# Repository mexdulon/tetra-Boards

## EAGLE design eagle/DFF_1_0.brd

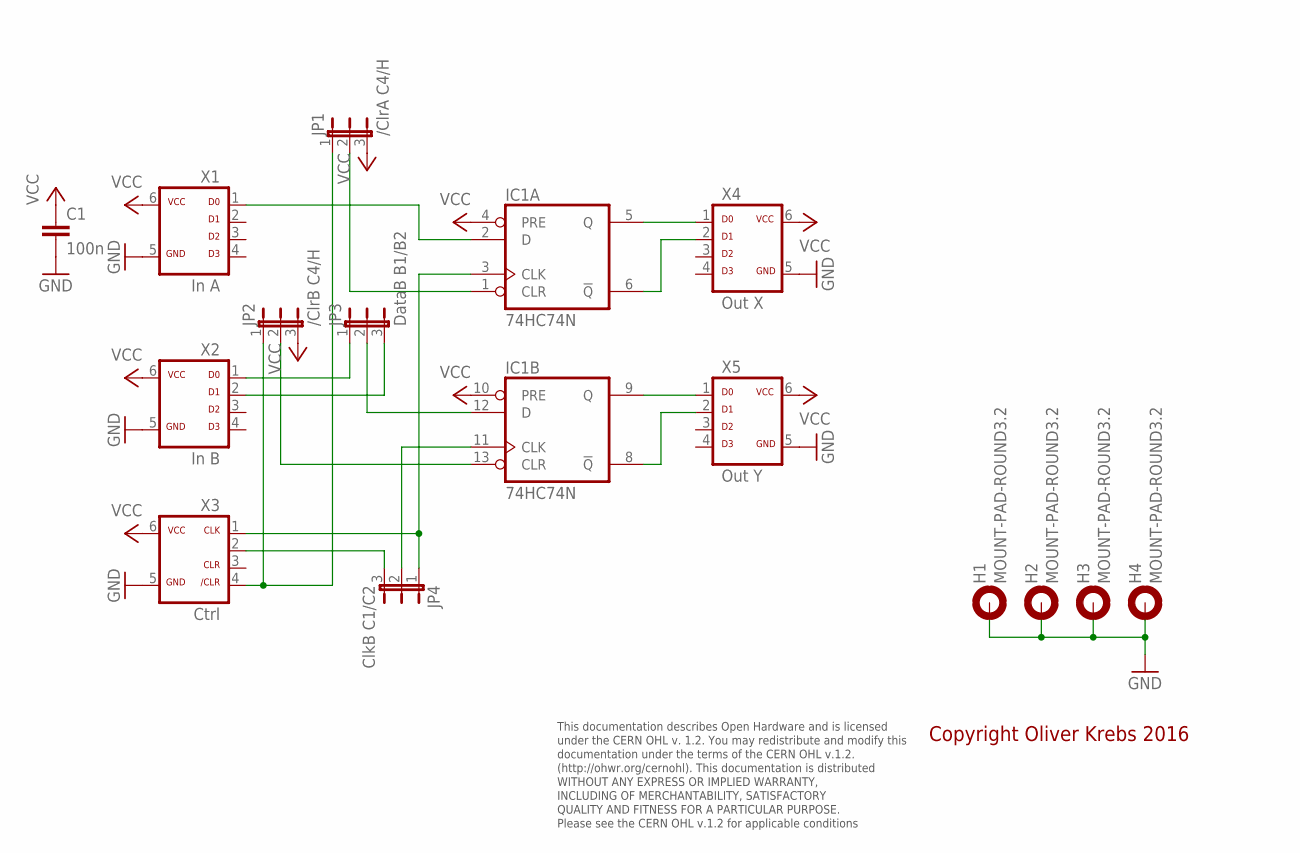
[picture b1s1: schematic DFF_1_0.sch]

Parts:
C1: 100n; C050-025X075
H1, H2, H3, H4: MOUNT-PAD-ROUND3.2; 3,2-PAD
IC1: 74HC74N; DIL14
JP1: /ClrA C4/H; JP2-U
JP2: /ClrB C4/H; JP2-U
JP3: DataB B1/B2; JP2-U
JP4: ClkB C1/C2; JP2-U
X1: In A; ML-6
X2: In B; ML-6
X3: Ctrl; ML-6
X4: Out X; ML-6
X5: Out Y; ML-6

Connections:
GND: C1.2, H1.B3,2, H2.B3,2, H3.B3,2, H4.B3,2, IC1.7 (GND), X1.5, X2.5, X3.5, X4.5, X5.5
unnamed: IC1.2 (D), X1.1
unnamed: IC1.3 (CLK), JP4.1, X3.1
unnamed: IC1.11 (CLK), JP4.2
unnamed: IC1.12 (D), JP3.2
unnamed: IC1.13 (CLR), JP2.2
unnamed: IC1.1 (CLR), JP1.2
unnamed: IC1.5 (Q), X4.1
unnamed: IC1.6 (!Q), X4.2
unnamed: IC1.9 (Q), X5.1
unnamed: IC1.8 (!Q), X5.2
unnamed: JP1.1, JP2.1, X3.4
unnamed: JP3.1, X2.1
unnamed: JP3.3, X2.2
unnamed: JP4.3, X3.2
VCC: C1.1, IC1.4 (PRE), IC1.10 (PRE), IC1.14 (VCC), JP1.3, JP2.3, X1.6, X2.6, X3.6, X4.6, X5.6

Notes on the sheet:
This documentation describes Open Hardware and is licensed under the CERN OHL v. 1.2. You may redistribute and modify this documentation under the terms of the CERN OHL v.1.2. (http://ohwr.org/cernohl). This documentation is distributed WITHOUT ANY EXPRESS OR IMPLIED WARRANTY, INCLUDING OF MERCHANT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
Copyright Oliver Krebs 2016

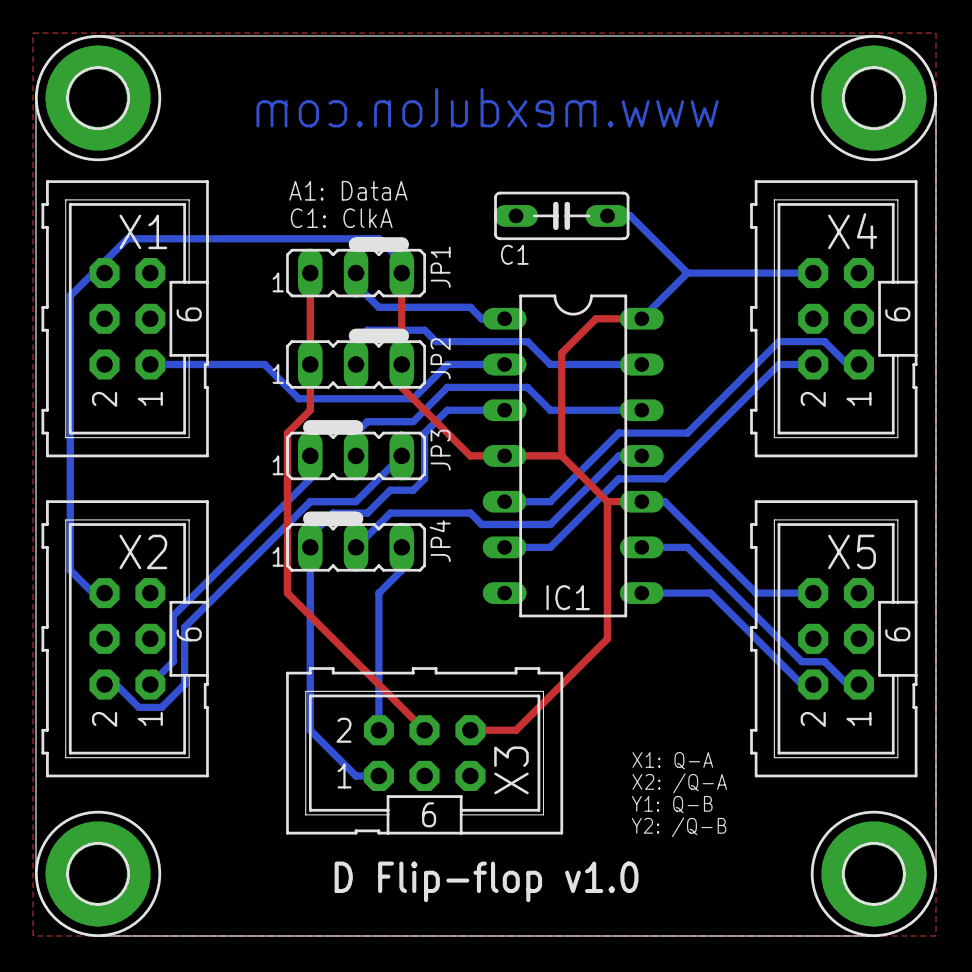
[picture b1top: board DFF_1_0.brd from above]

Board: 2 copper layers, 50.0 x 50.0 mm, 15 parts (0 on the bottom side), 16 nets.

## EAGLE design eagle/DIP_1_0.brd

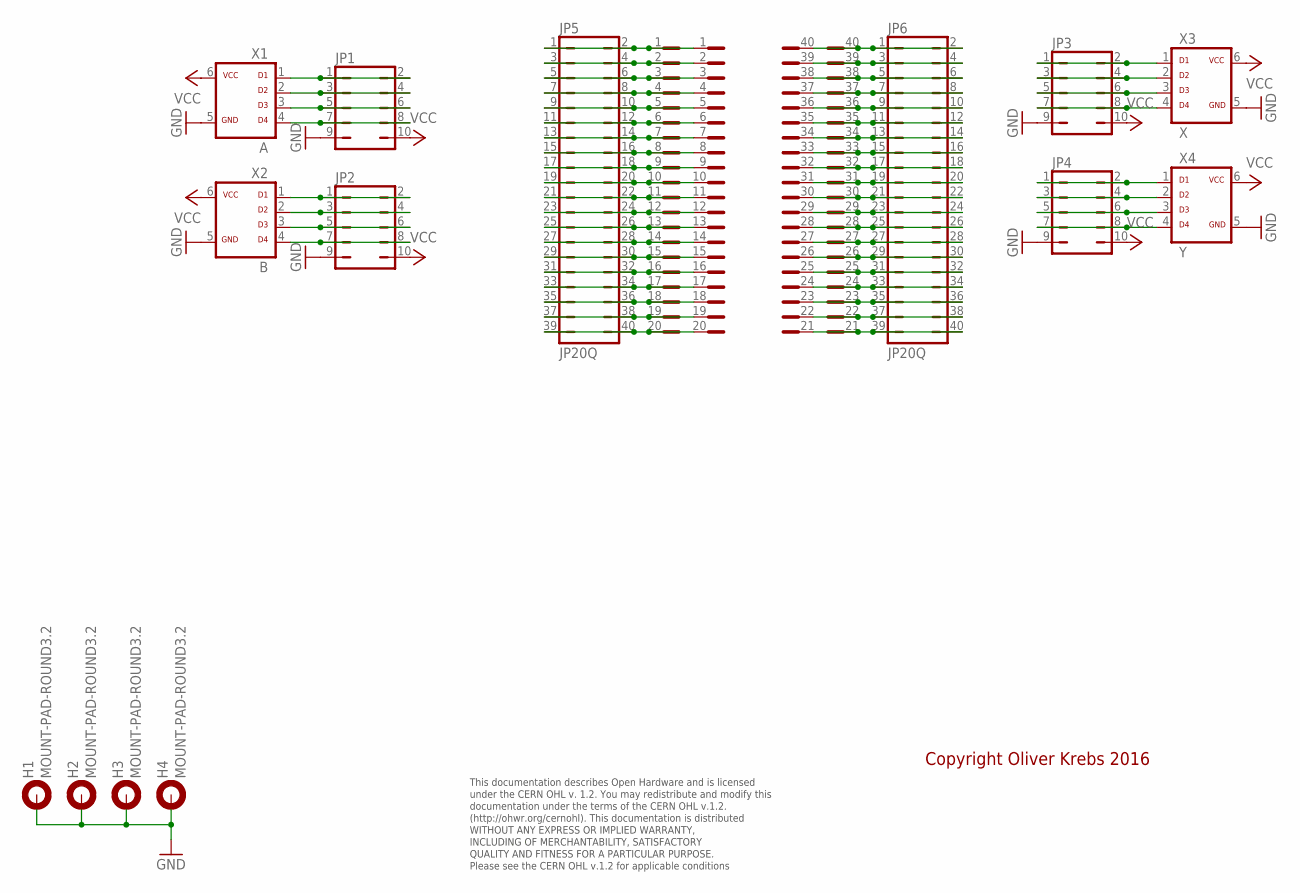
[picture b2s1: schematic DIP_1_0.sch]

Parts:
H1, H2, H3, H4: MOUNT-PAD-ROUND3.2; 3,2-PAD
JP1, JP2, JP3, JP4: JP5Q
JP5, JP6: JP20Q
X1: A; ML-6
X2: B; ML-6
X3: X; ML-6
X4: Y; ML-6
X5: DIL40-3
X6: DIL40-6

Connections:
GND: H1.B3,2, H2.B3,2, H3.B3,2, H4.B3,2, JP1.9, JP2.9, JP3.9, JP4.9, X1.5, X2.5, X3.5, X4.5
unnamed: JP3.1, JP3.2, X3.1
unnamed: JP3.3, JP3.4, X3.2
unnamed: JP3.5, JP3.6, X3.3
unnamed: JP3.7, JP3.8, X3.4
unnamed: JP4.1, JP4.2, X4.1
unnamed: JP4.3, JP4.4, X4.2
unnamed: JP4.5, JP4.6, X4.3
unnamed: JP4.7, JP4.8, X4.4
unnamed: JP1.1, JP1.2, X1.1
unnamed: JP1.3, JP1.4, X1.2
unnamed: JP1.5, JP1.6, X1.3
unnamed: JP1.7, JP1.8, X1.4
unnamed: JP2.1, JP2.2, X2.1
unnamed: JP2.3, JP2.4, X2.2
unnamed: JP2.5, JP2.6, X2.3
unnamed: JP2.7, JP2.8, X2.4
unnamed: JP5.1, JP5.2, X5.1, X6.1
unnamed: JP5.3, JP5.4, X5.2, X6.2
unnamed: JP5.5, JP5.6, X5.3, X6.3
unnamed: JP5.7, JP5.8, X5.4, X6.4
unnamed: JP5.9, JP5.10, X5.5, X6.5
unnamed: JP5.11, JP5.12, X5.6, X6.6
unnamed: JP5.13, JP5.14, X5.7, X6.7
unnamed: JP5.15, JP5.16, X5.8, X6.8
unnamed: JP5.17, JP5.18, X5.9, X6.9
unnamed: JP5.19, JP5.20, X5.10, X6.10
unnamed: JP5.21, JP5.22, X5.11, X6.11
unnamed: JP5.23, JP5.24, X5.12, X6.12
unnamed: JP5.25, JP5.26, X5.13, X6.13
unnamed: JP5.27, JP5.28, X5.14, X6.14
unnamed: JP5.29, JP5.30, X5.15, X6.15
unnamed: JP5.31, JP5.32, X5.16, X6.16
unnamed: JP5.33, JP5.34, X5.17, X6.17
unnamed: JP5.35, JP5.36, X5.18, X6.18
unnamed: JP5.37, JP5.38, X5.19, X6.19
unnamed: JP5.39, JP5.40, X5.20, X6.20
unnamed: JP6.1, JP6.2, X5.40, X6.40
unnamed: JP6.3, JP6.4, X5.39, X6.39
unnamed: JP6.5, JP6.6, X5.38, X6.38
unnamed: JP6.7, JP6.8, X5.37, X6.37
unnamed: JP6.9, JP6.10, X5.36, X6.36
unnamed: JP6.11, JP6.12, X5.35, X6.35
unnamed: JP6.13, JP6.14, X5.34, X6.34
unnamed: JP6.15, JP6.16, X5.33, X6.33
unnamed: JP6.17, JP6.18, X5.32, X6.32
unnamed: JP6.19, JP6.20, X5.31, X6.31
unnamed: JP6.21, JP6.22, X5.30, X6.30
unnamed: JP6.23, JP6.24, X5.29, X6.29
unnamed: JP6.25, JP6.26, X5.28, X6.28
unnamed: JP6.27, JP6.28, X5.27, X6.27
unnamed: JP6.29, JP6.30, X5.26, X6.26
unnamed: JP6.31, JP6.32, X5.25, X6.25
unnamed: JP6.33, JP6.34, X5.24, X6.24
unnamed: JP6.35, JP6.36, X5.23, X6.23
unnamed: JP6.37, JP6.38, X5.22, X6.22
unnamed: JP6.39, JP6.40, X5.21, X6.21
VCC: JP1.10, JP2.10, JP3.10, JP4.10, X1.6, X2.6, X3.6, X4.6

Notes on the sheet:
This documentation describes Open Hardware and is licensed under the CERN OHL v. 1.2. You may redistribute and modify this documentation under the terms of the CERN OHL v.1.2. (http://ohwr.org/cernohl). This documentation is distributed WITHOUT ANY EXPRESS OR IMPLIED WARRANTY, INCLUDING OF MERCHANT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
Copyright Oliver Krebs 2016

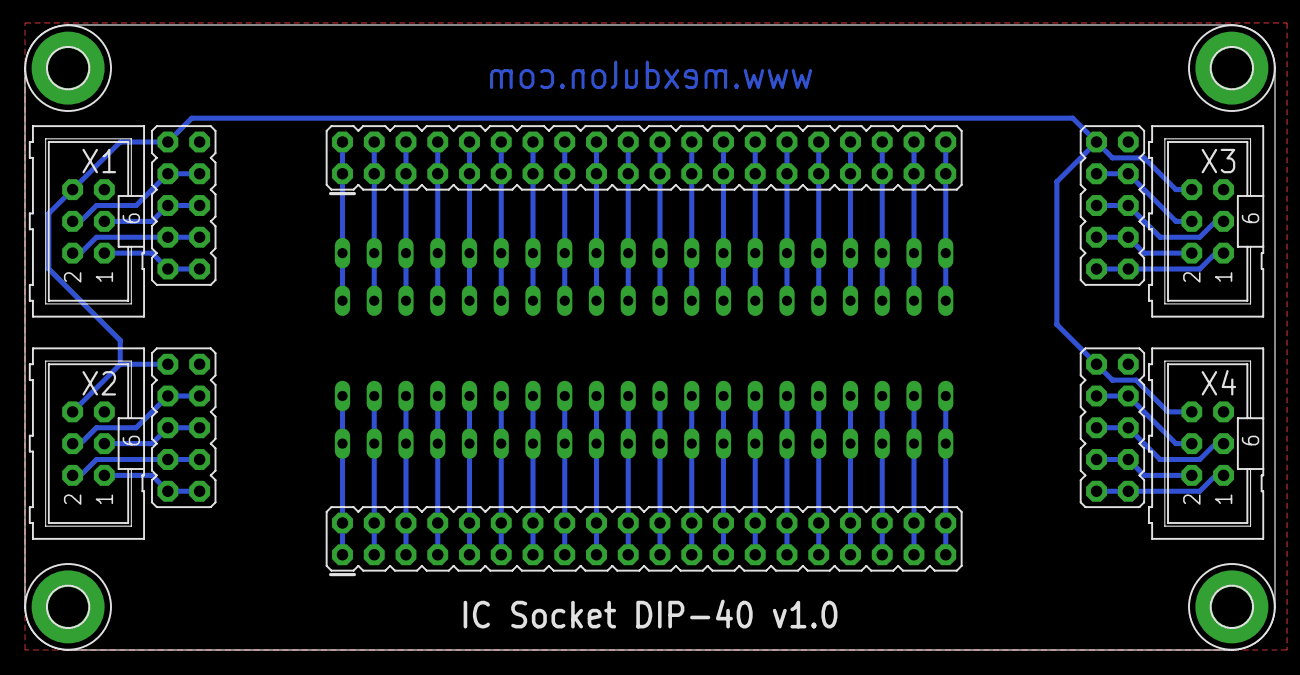
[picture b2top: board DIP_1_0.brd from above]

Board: 2 copper layers, 100.0 x 50.0 mm, 16 parts (0 on the bottom side), 58 nets.

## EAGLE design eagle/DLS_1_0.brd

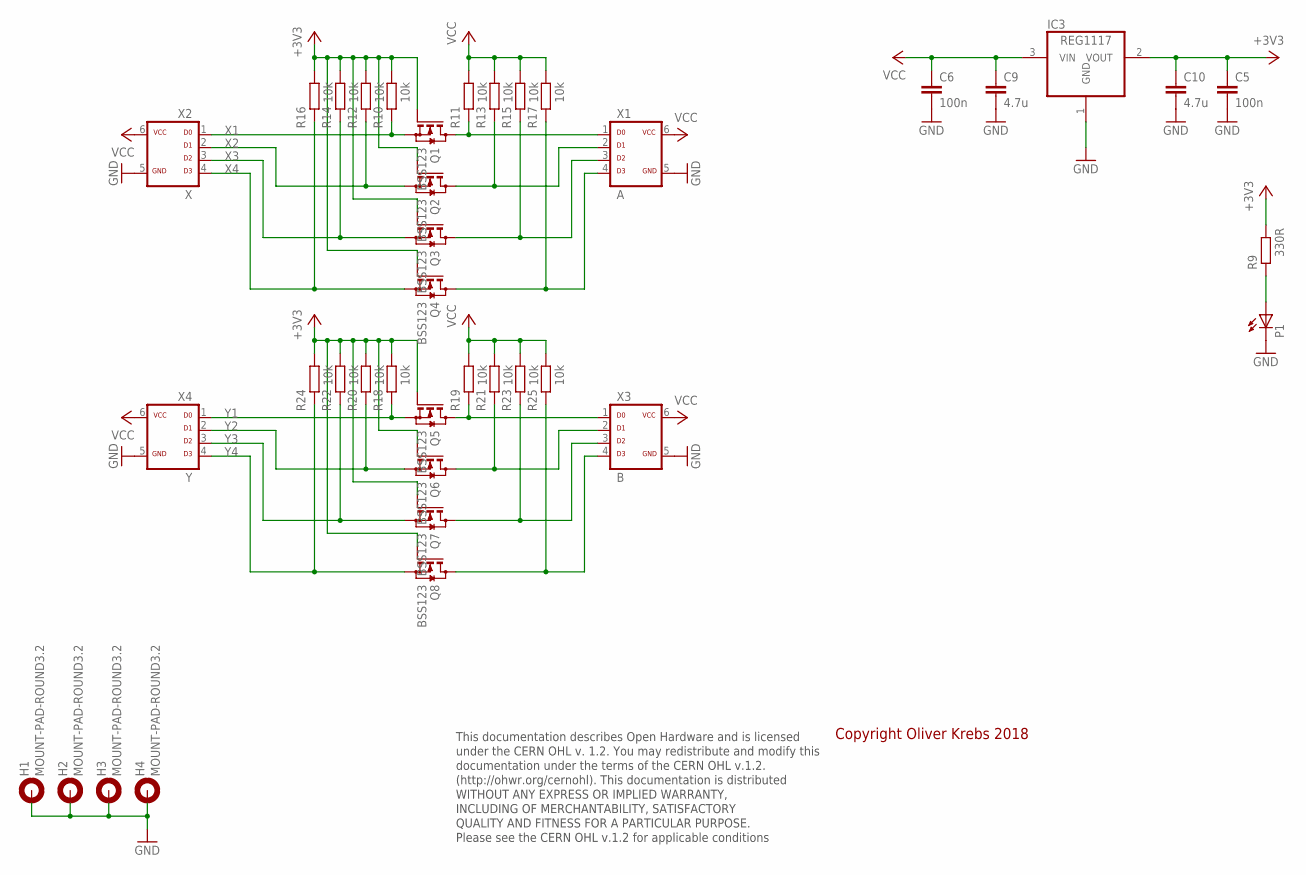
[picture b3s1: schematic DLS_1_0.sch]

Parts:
C5, C6: 100n; C0603
C9, C10: 4.7u; C0805K
H1, H2, H3, H4: MOUNT-PAD-ROUND3.2; 3,2-PAD
IC3: REG1117; SOT223
P1: LEDCHIPLED_1206; CHIPLED_1206
Q1, Q2, Q3, Q4, Q5, Q6, Q7, Q8: BSS123; SOT23
R9: 330R; R0402
R10, R11, R12, R13, R14, R15, R16, R17, R18, R19, R20, R21, R22, R23, R24, R25: 10k; R0402
X1: A; ML-6
X2: X; ML-6
X3: B; ML-6
X4: Y; ML-6

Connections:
+3V3: C5.1, C10.1, IC3.2 (VOUT), Q1.1 (G), Q2.1 (G), Q3.1 (G), Q4.1 (G), Q5.1 (G), Q6.1 (G), Q7.1 (G), Q8.1 (G), R9.2, R10.2, R12.2, R14.2, R16.2, R18.2, R20.2, R22.2, R24.2
GND: C5.2, C6.2, C9.2, C10.2, H1.B3,2, H2.B3,2, H3.B3,2, H4.B3,2, IC3.1 (GND), P1.C, X1.5, X2.5, X3.5, X4.5
unnamed: Q1.3 (D), R11.1, X1.1
unnamed: Q5.3 (D), R19.1, X3.1
unnamed: Q2.3 (D), R13.1, X1.2
unnamed: Q3.3 (D), R15.1, X1.3
unnamed: Q4.3 (D), R17.1, X1.4
unnamed: Q6.3 (D), R21.1, X3.2
unnamed: Q7.3 (D), R23.1, X3.3
unnamed: Q8.3 (D), R25.1, X3.4
unnamed: P1.A, R9.1
VCC: C6.1, C9.1, IC3.3 (VIN), R11.2, R13.2, R15.2, R17.2, R19.2, R21.2, R23.2, R25.2, X1.6, X2.6, X3.6, X4.6
X1: Q1.2 (S), R10.1, X2.1
X2: Q2.2 (S), R12.1, X2.2
X3: Q3.2 (S), R14.1, X2.3
X4: Q4.2 (S), R16.1, X2.4
Y1: Q5.2 (S), R18.1, X4.1
Y2: Q6.2 (S), R20.1, X4.2
Y3: Q7.2 (S), R22.1, X4.3
Y4: Q8.2 (S), R24.1, X4.4

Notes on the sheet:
This documentation describes Open Hardware and is licensed under the CERN OHL v. 1.2. You may redistribute and modify this documentation under the terms of the CERN OHL v.1.2. (http://ohwr.org/cernohl). This documentation is distributed WITHOUT ANY EXPRESS OR IMPLIED WARRANTY, INCLUDING OF MERCHANT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
Copyright Oliver Krebs 2018

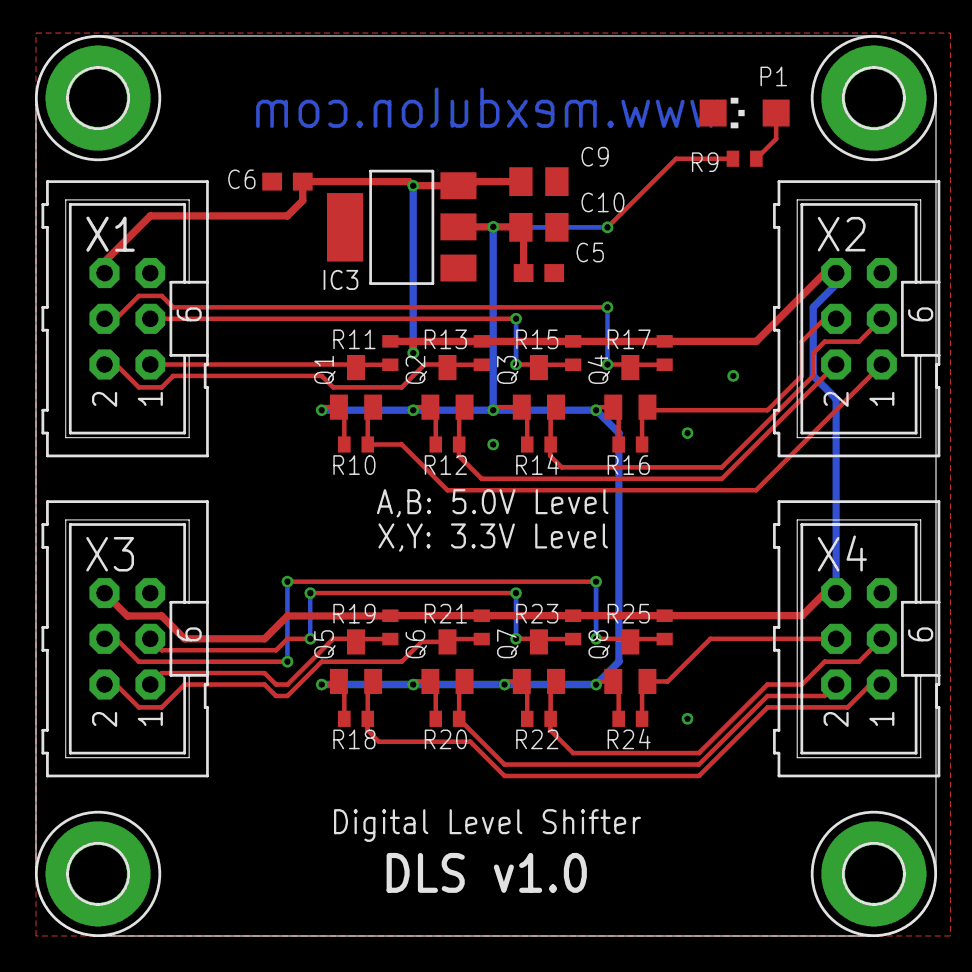
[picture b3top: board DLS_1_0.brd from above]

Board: 2 copper layers, 50.0 x 50.0 mm, 39 parts (0 on the bottom side), 20 nets.

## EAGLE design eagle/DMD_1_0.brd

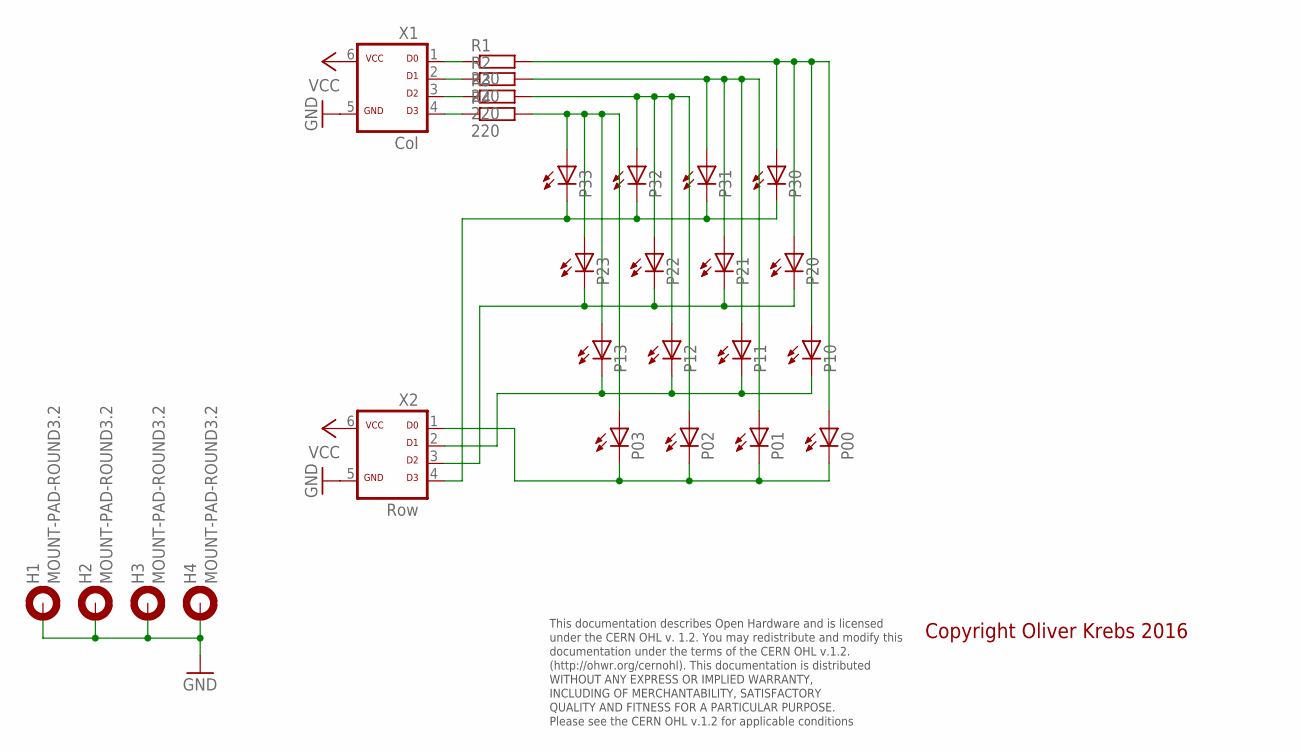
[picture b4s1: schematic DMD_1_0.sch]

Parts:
H1, H2, H3, H4: MOUNT-PAD-ROUND3.2; 3,2-PAD
P00, P01, P02, P03, P10, P11, P12, P13, P20, P21, P22, P23, P30, P31, P32, P33: LED5MM
R1, R2, R3, R4: 220; 0207/10
X1: Col; ML-6
X2: Row; ML-6

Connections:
COL1: P00.A, P10.A, P20.A, P30.A, R1.2
GND: H1.B3,2, H2.B3,2, H3.B3,2, H4.B3,2, X1.5, X2.5
unnamed: P01.A, P11.A, P21.A, P31.A, R2.2
unnamed: R1.1, X1.1
unnamed: R2.1, X1.2
unnamed: R3.1, X1.3
unnamed: R4.1, X1.4
P13: P02.A, P12.A, P22.A, P32.A, R3.2
P34: P03.A, P13.A, P23.A, P33.A, R4.2
ROW1: P00.K (C), P01.K (C), P02.K (C), P03.K (C), X2.1
ROW2: P10.K (C), P11.K (C), P12.K (C), P13.K (C), X2.2
ROW3: P20.K (C), P21.K (C), P22.K (C), P23.K (C), X2.3
ROW4: P30.K (C), P31.K (C), P32.K (C), P33.K (C), X2.4
VCC: X1.6, X2.6

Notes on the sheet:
This documentation describes Open Hardware and is licensed under the CERN OHL v. 1.2. You may redistribute and modify this documentation under the terms of the CERN OHL v.1.2. (http://ohwr.org/cernohl). This documentation is distributed WITHOUT ANY EXPRESS OR IMPLIED WARRANTY, INCLUDING OF MERCHANT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
Copyright Oliver Krebs 2016

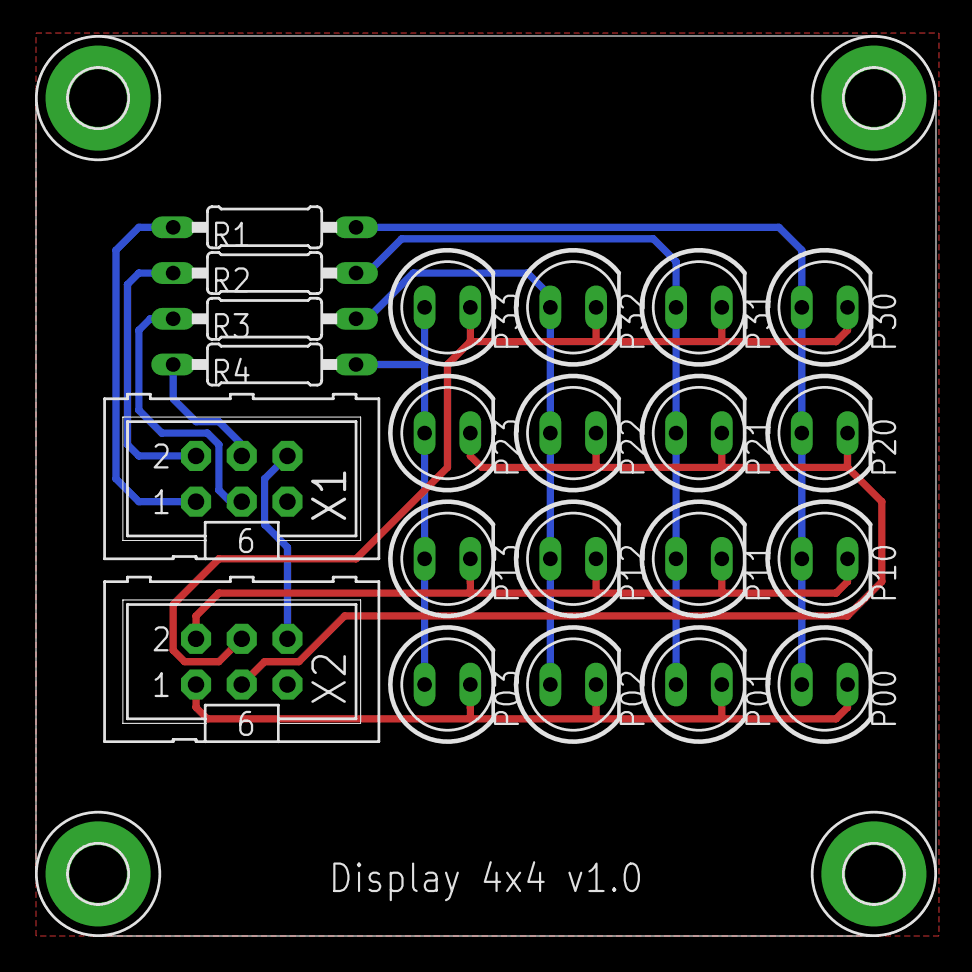
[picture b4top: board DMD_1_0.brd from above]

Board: 2 copper layers, 50.0 x 50.0 mm, 26 parts (0 on the bottom side), 14 nets.

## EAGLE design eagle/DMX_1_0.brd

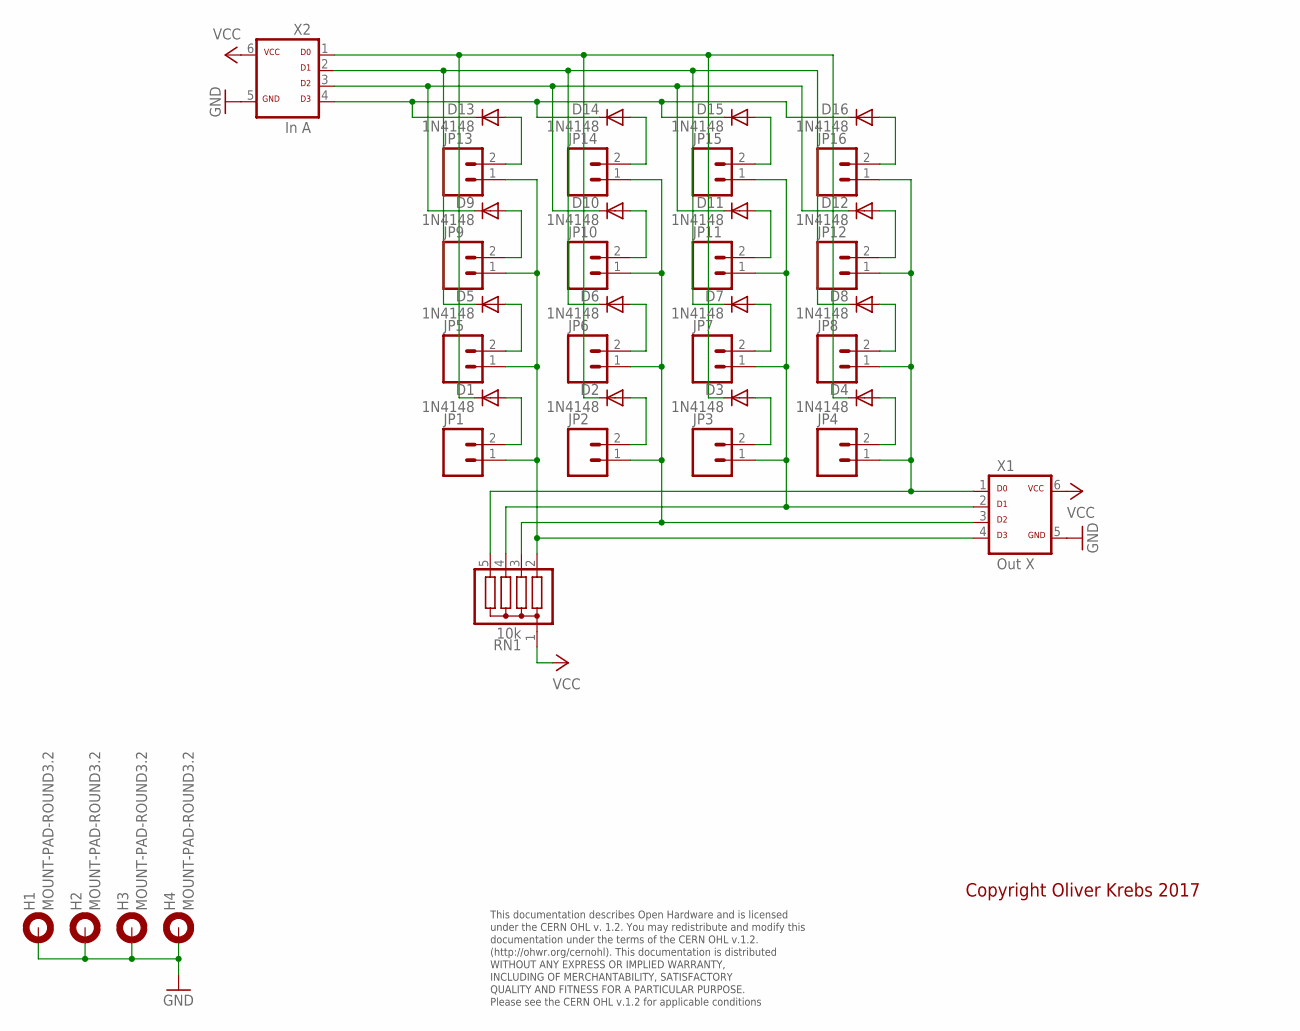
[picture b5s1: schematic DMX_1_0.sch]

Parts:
D1, D2, D3, D4, D5, D6, D7, D8, D9, D10, D11, D12, D13, D14, D15, D16: 1N4148; DO35-7
H1, H2, H3, H4: MOUNT-PAD-ROUND3.2; 3,2-PAD
JP1, JP2, JP3, JP4, JP5, JP6, JP7, JP8, JP9, JP10, JP11, JP12, JP13, JP14, JP15, JP16: M02PTH; 1X02
RN1: 10k; SIL5
X1: Out X; ML-6
X2: In A; ML-6

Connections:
GND: H1.B3,2, H2.B3,2, H3.B3,2, H4.B3,2, X1.5, X2.5
unnamed: JP4.1, JP8.1, JP12.1, JP16.1, RN1.5, X1.1
unnamed: JP3.1, JP7.1, JP11.1, JP15.1, RN1.4, X1.2
unnamed: JP2.1, JP6.1, JP10.1, JP14.1, RN1.3, X1.3
unnamed: JP1.1, JP5.1, JP9.1, JP13.1, RN1.2, X1.4
unnamed: D1.C, D2.C, D3.C, D4.C, X2.1
unnamed: D1.A, JP1.2
unnamed: D2.A, JP2.2
unnamed: D3.A, JP3.2
unnamed: D4.A, JP4.2
unnamed: D5.C, D6.C, D7.C, D8.C, X2.2
unnamed: D6.A, JP6.2
unnamed: D7.A, JP7.2
unnamed: D5.A, JP5.2
unnamed: D8.A, JP8.2
unnamed: D9.A, JP9.2
unnamed: D10.A, JP10.2
unnamed: D11.A, JP11.2
unnamed: D12.A, JP12.2
unnamed: D9.C, D10.C, D11.C, D12.C, X2.3
unnamed: D13.C, D14.C, D15.C, D16.C, X2.4
unnamed: D13.A, JP13.2
unnamed: D14.A, JP14.2
unnamed: D15.A, JP15.2
unnamed: D16.A, JP16.2
VCC: RN1.1, X1.6, X2.6

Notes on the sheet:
This documentation describes Open Hardware and is licensed under the CERN OHL v. 1.2. You may redistribute and modify this documentation under the terms of the CERN OHL v.1.2. (http://ohwr.org/cernohl). This documentation is distributed WITHOUT ANY EXPRESS OR IMPLIED WARRANTY, INCLUDING OF MERCHANT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
Copyright Oliver Krebs 2017

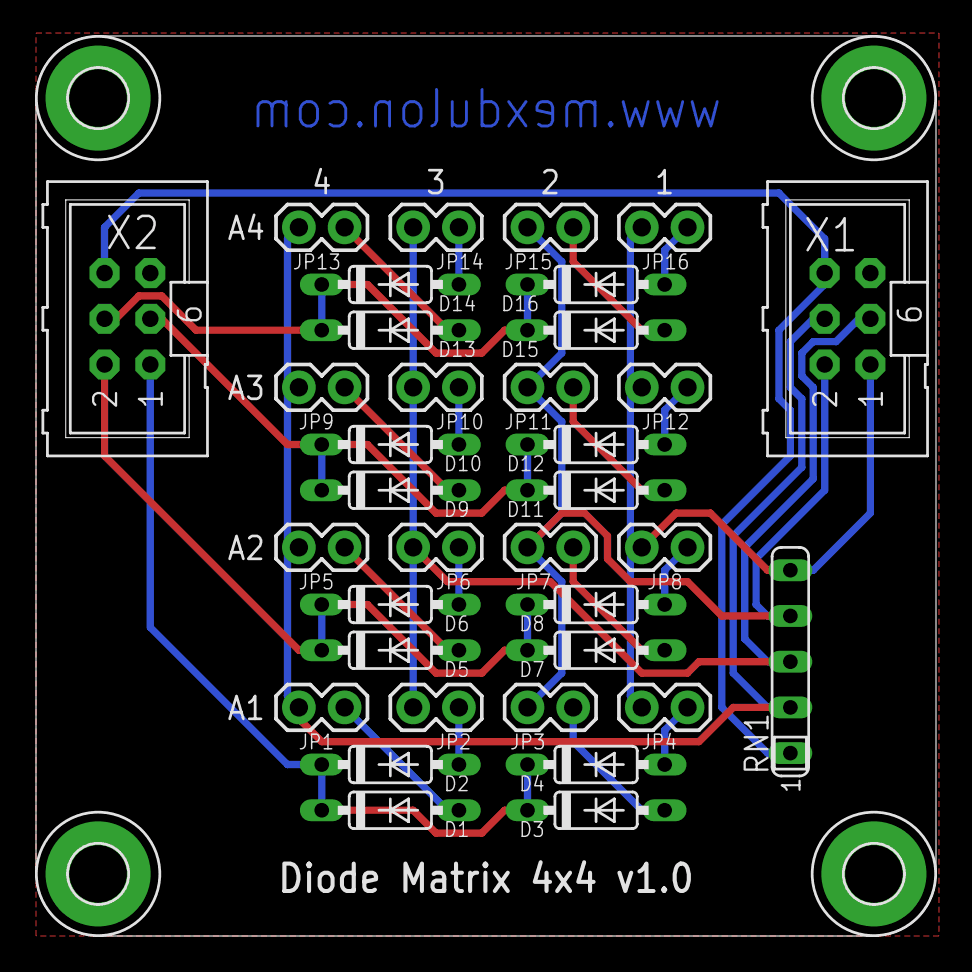
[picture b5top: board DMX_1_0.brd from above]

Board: 2 copper layers, 50.0 x 50.0 mm, 39 parts (0 on the bottom side), 26 nets.

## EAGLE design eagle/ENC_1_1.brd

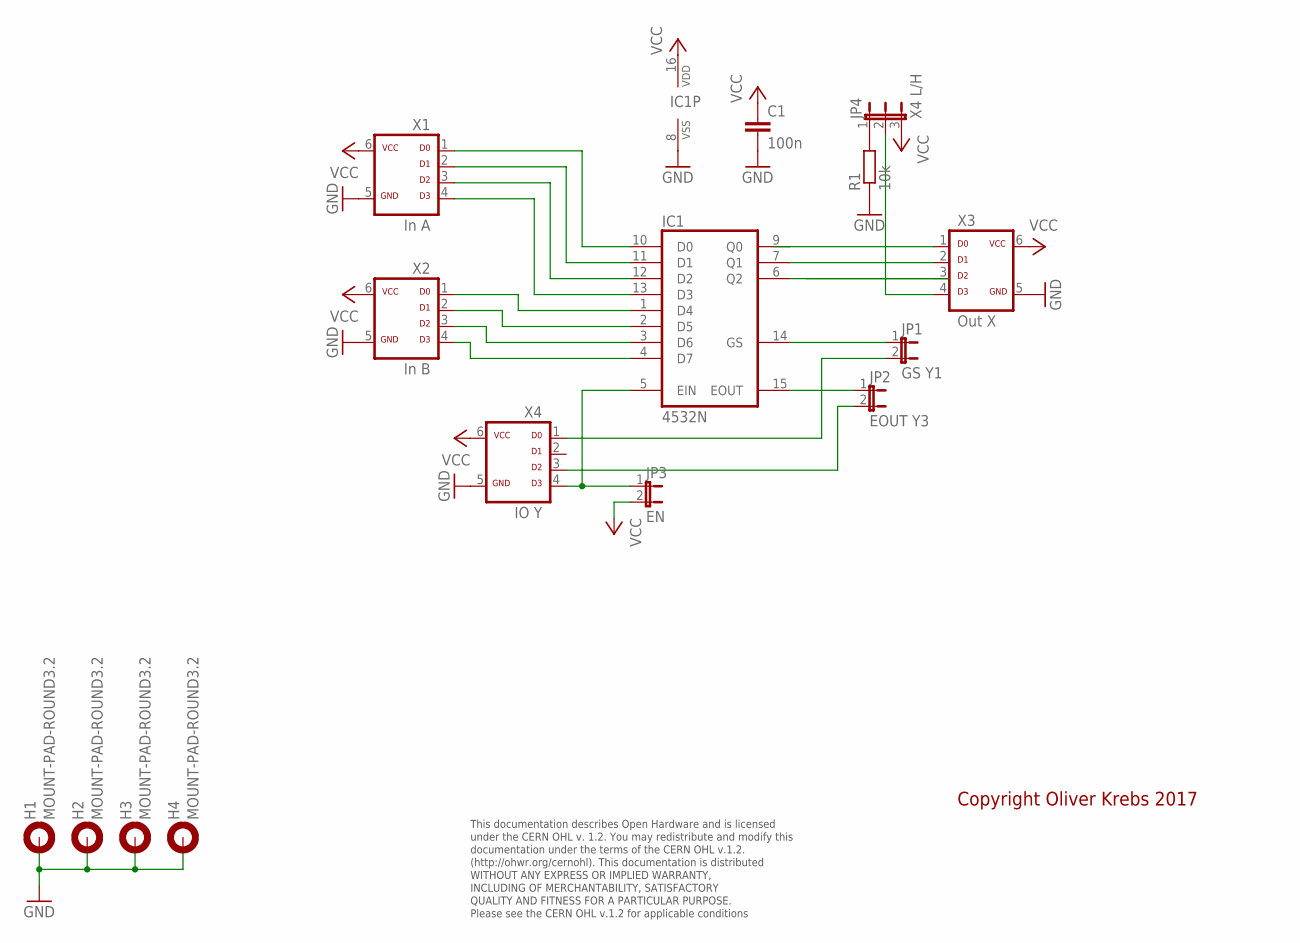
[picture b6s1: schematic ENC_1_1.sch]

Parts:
C1: 100n; C050-025X075
H1, H2, H3, H4: MOUNT-PAD-ROUND3.2; 3,2-PAD
IC1: 4532N; DIL16
JP1: GS Y1; JP1
JP2: EOUT Y3; JP1
JP3: EN; JP1
JP4: X4 L/H; JP2-U
R1: 10k; 0207/10
X1: In A; ML-6
X2: In B; ML-6
X3: Out X; ML-6
X4: IO Y; ML-6

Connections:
GND: C1.2, H1.B3,2, H2.B3,2, H3.B3,2, H4.B3,2, IC1.8 (VSS), R1.1, X1.5, X2.5, X3.5, X4.5
unnamed: IC1.9 (Q0), X3.1
unnamed: IC1.7 (Q1), X3.2
unnamed: IC1.6 (Q2), X3.3
unnamed: IC1.1 (D4), X2.1
unnamed: IC1.2 (D5), X2.2
unnamed: IC1.3 (D6), X2.3
unnamed: IC1.4 (D7), X2.4
unnamed: IC1.13 (D3), X1.4
unnamed: IC1.12 (D2), X1.3
unnamed: IC1.11 (D1), X1.2
unnamed: IC1.10 (D0), X1.1
unnamed: IC1.5 (EIN), JP3.1, X4.4
unnamed: IC1.14 (GS), JP1.1
unnamed: JP1.2, X4.1
unnamed: JP2.2, X4.3
unnamed: IC1.15 (EOUT), JP2.1
unnamed: JP4.2, X3.4
unnamed: JP4.1, R1.2
VCC: C1.1, IC1.16 (VDD), JP3.2, JP4.3, X1.6, X2.6, X3.6, X4.6

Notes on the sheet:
This documentation describes Open Hardware and is licensed under the CERN OHL v. 1.2. You may redistribute and modify this documentation under the terms of the CERN OHL v.1.2. (http://ohwr.org/cernohl). This documentation is distributed WITHOUT ANY EXPRESS OR IMPLIED WARRANTY, INCLUDING OF MERCHANT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
Copyright Oliver Krebs 2017

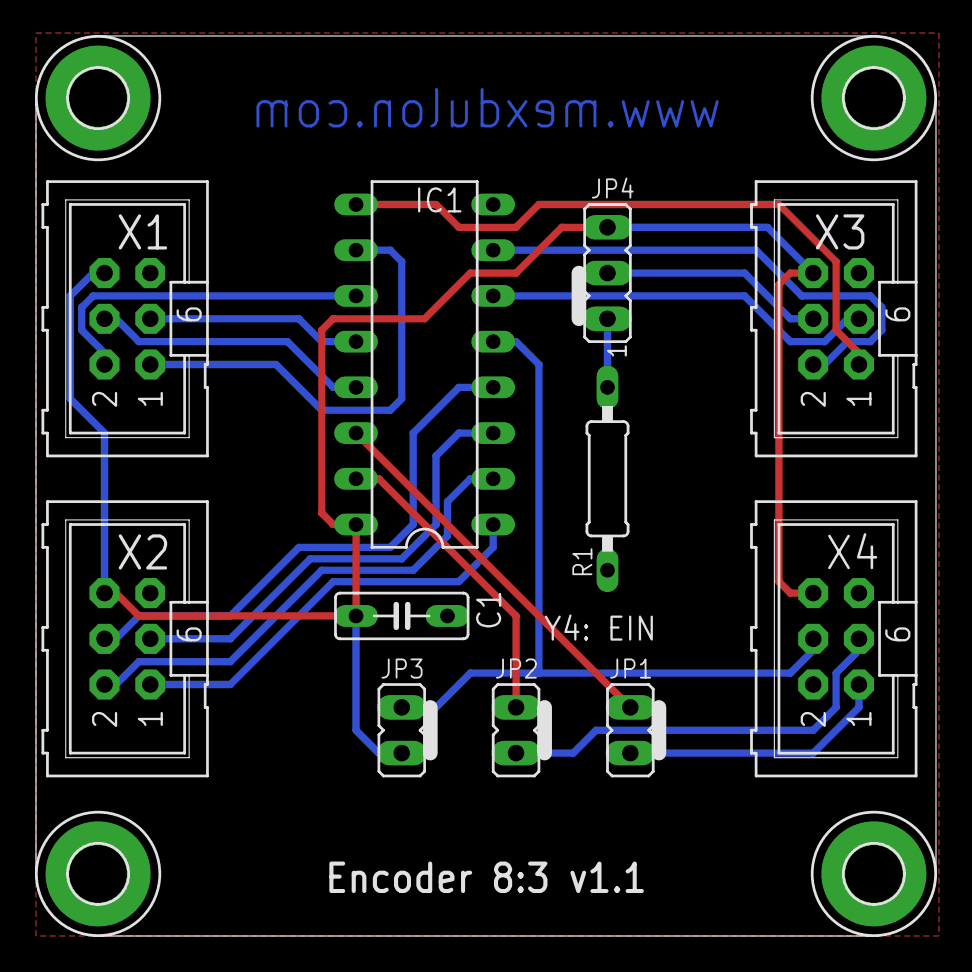
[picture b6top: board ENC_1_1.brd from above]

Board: 2 copper layers, 50.0 x 50.0 mm, 15 parts (0 on the bottom side), 20 nets.

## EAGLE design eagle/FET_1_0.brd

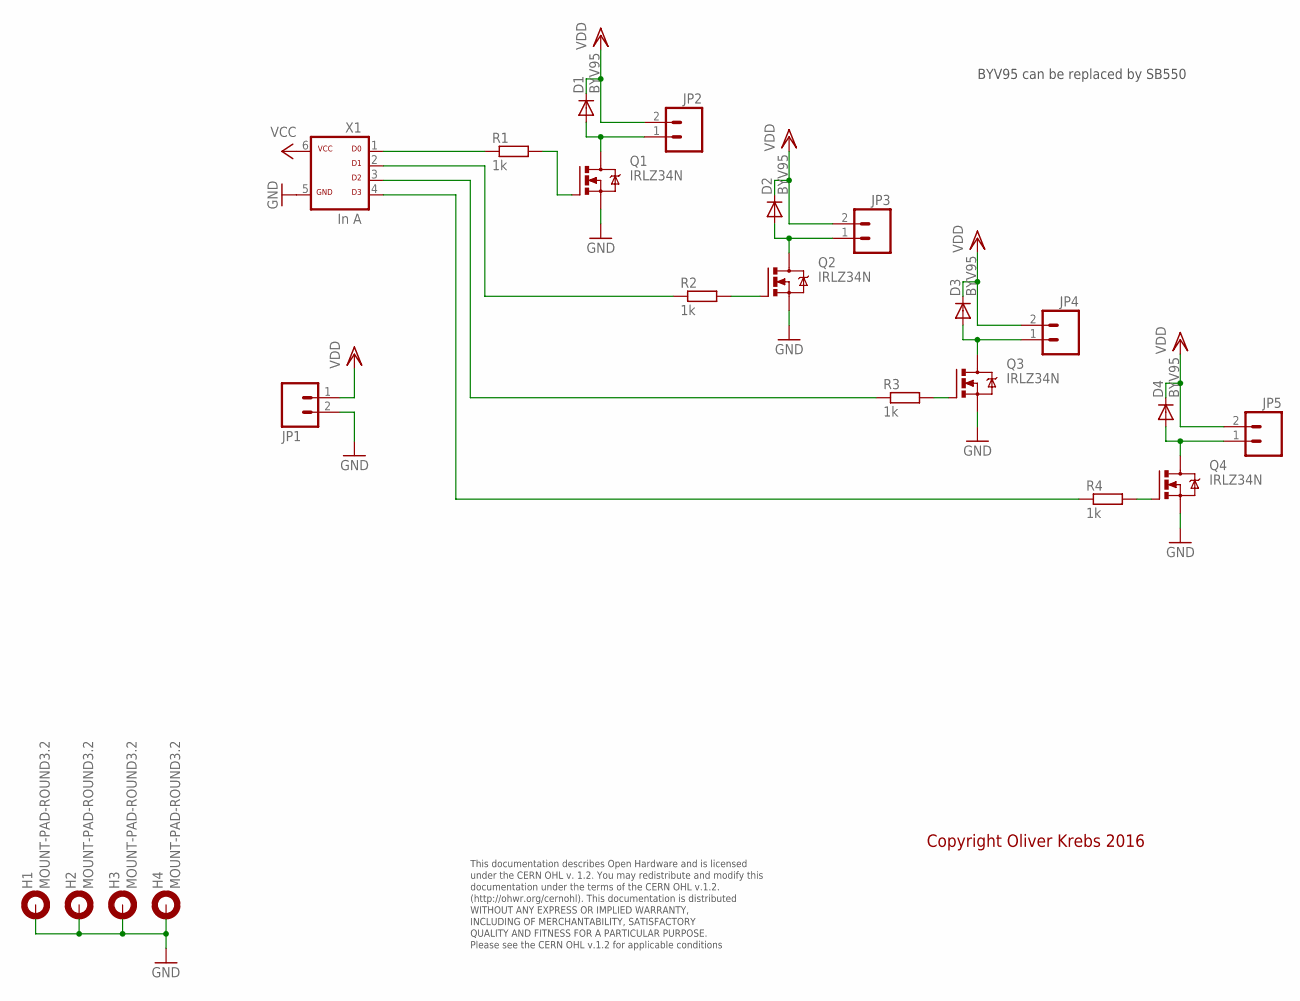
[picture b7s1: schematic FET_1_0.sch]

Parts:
D1, D2, D3, D4: BYV95; SOD57-10
H1, H2, H3, H4: MOUNT-PAD-ROUND3.2; 3,2-PAD
JP1, JP2, JP3, JP4, JP5: M021.3MM-5.08; 1X02_BIG_5.08
Q1, Q2, Q3, Q4: IRLZ34N; TO220BV
R1, R2, R3, R4: 1k; 0207/10
X1: In A; ML-6

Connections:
GND: H1.B3,2, H2.B3,2, H3.B3,2, H4.B3,2, JP1.2, Q1.S, Q2.S, Q3.S, Q4.S, X1.5
unnamed: Q1.G, R1.2
unnamed: Q2.G, R2.2
unnamed: D1.A, JP2.1, Q1.D
unnamed: Q3.G, R3.2
unnamed: Q4.G, R4.2
unnamed: D2.A, JP3.1, Q2.D
unnamed: D3.A, JP4.1, Q3.D
unnamed: D4.A, JP5.1, Q4.D
unnamed: R1.1, X1.1
unnamed: R2.1, X1.2
unnamed: R3.1, X1.3
unnamed: R4.1, X1.4
VCC: X1.6
VDD: D1.C, D2.C, D3.C, D4.C, JP1.1, JP2.2, JP3.2, JP4.2, JP5.2

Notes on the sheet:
This documentation describes Open Hardware and is licensed under the CERN OHL v. 1.2. You may redistribute and modify this documentation under the terms of the CERN OHL v.1.2. (http://ohwr.org/cernohl). This documentation is distributed WITHOUT ANY EXPRESS OR IMPLIED WARRANTY, INCLUDING OF MERCHANT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
Copyright Oliver Krebs 2016
BYV95 can be replaced by SB550

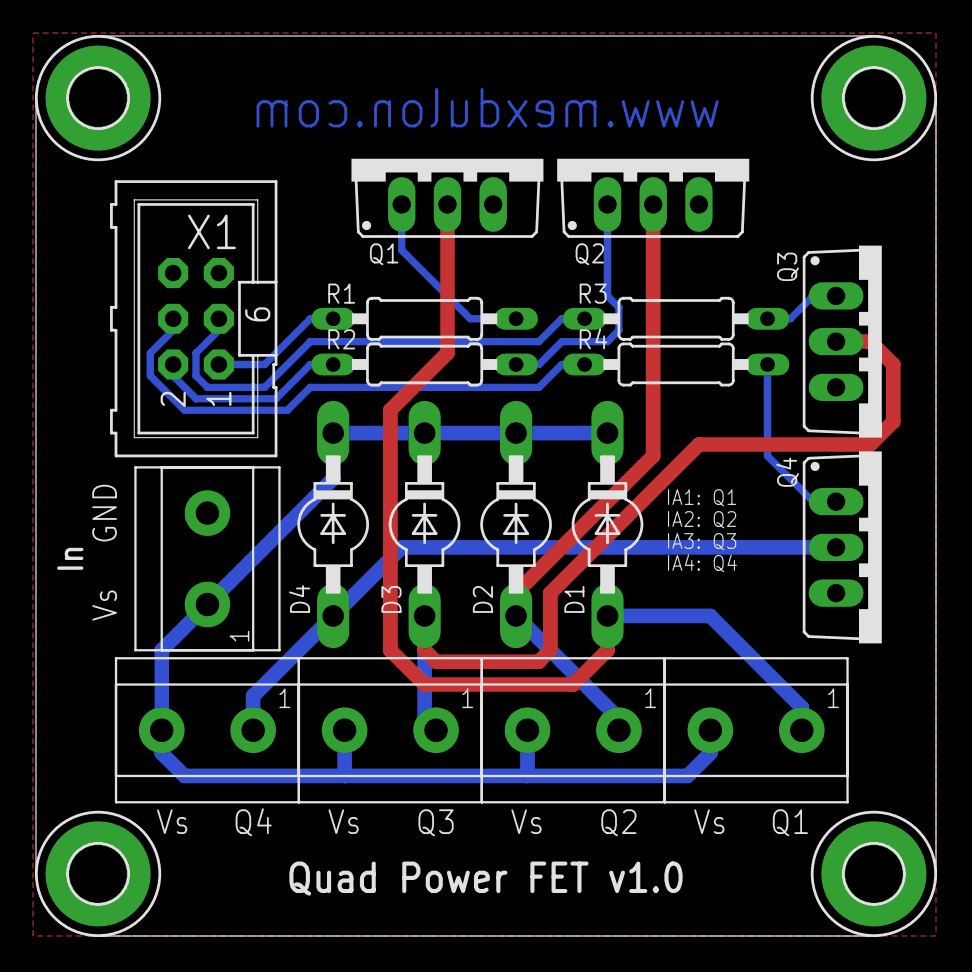
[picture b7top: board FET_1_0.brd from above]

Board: 2 copper layers, 50.0 x 50.0 mm, 22 parts (0 on the bottom side), 14 nets.

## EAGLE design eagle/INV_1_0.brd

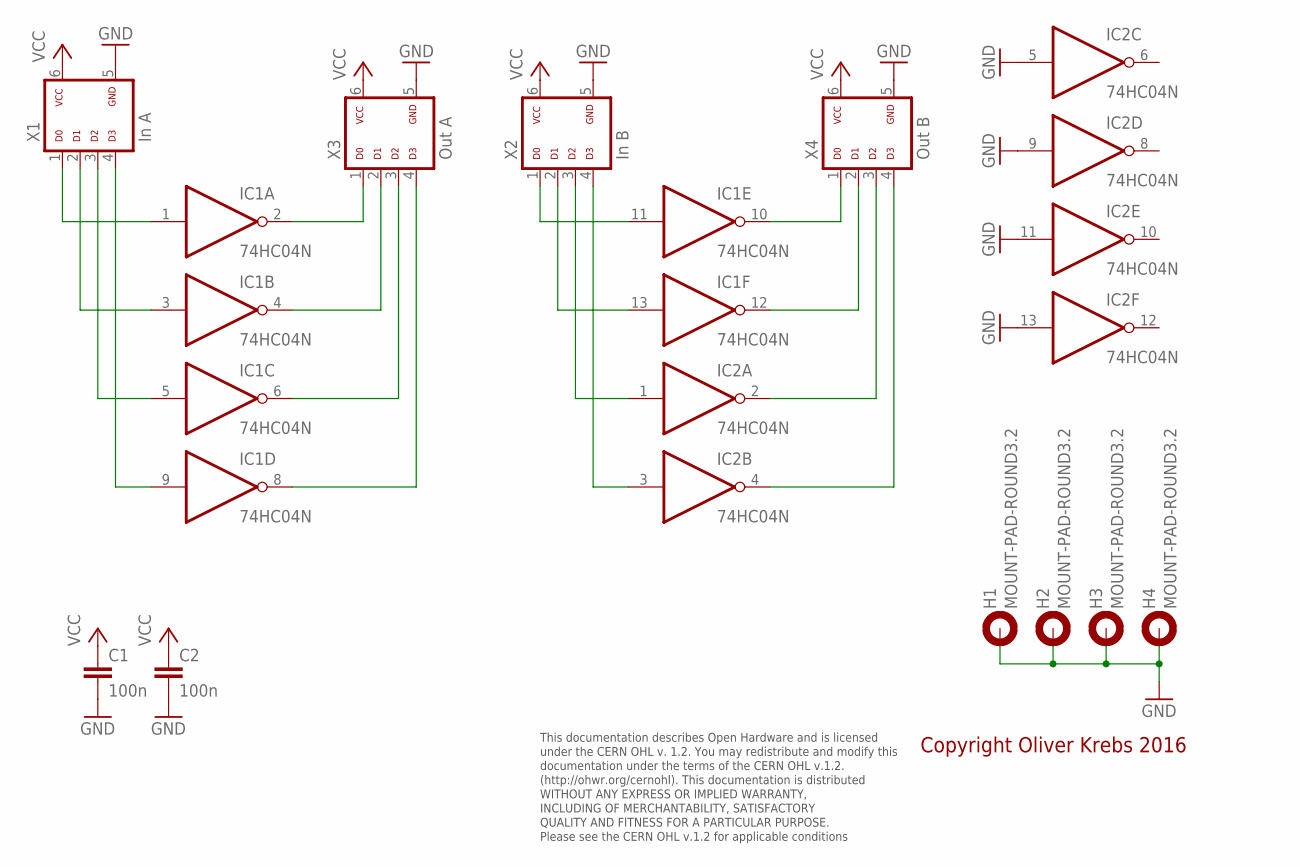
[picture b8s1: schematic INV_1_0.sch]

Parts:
C1, C2: 100n; C050-025X075
H1, H2, H3, H4: MOUNT-PAD-ROUND3.2; 3,2-PAD
IC1, IC2: 74HC04N; DIL14
X1: In A; ML-6
X2: In B; ML-6
X3: Out A; ML-6
X4: Out B; ML-6

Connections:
GND: C1.2, C2.2, H1.B3,2, H2.B3,2, H3.B3,2, H4.B3,2, IC1.7 (GND), IC2.5 (I), IC2.7 (GND), IC2.9 (I), IC2.11 (I), IC2.13 (I), X1.5, X2.5, X3.5, X4.5
unnamed: IC1.8 (O), X3.4
unnamed: IC1.10 (O), X4.1
unnamed: IC1.12 (O), X4.2
unnamed: IC2.2 (O), X4.3
unnamed: IC2.4 (O), X4.4
unnamed: IC1.1 (I), X1.1
unnamed: IC1.11 (I), X2.1
unnamed: IC1.13 (I), X2.2
unnamed: IC1.3 (I), X1.2
unnamed: IC1.5 (I), X1.3
unnamed: IC2.1 (I), X2.3
unnamed: IC1.9 (I), X1.4
unnamed: IC2.3 (I), X2.4
unnamed: IC1.2 (O), X3.1
unnamed: IC1.4 (O), X3.2
unnamed: IC1.6 (O), X3.3
VCC: C1.1, C2.1, IC1.14 (VCC), IC2.14 (VCC), X1.6, X2.6, X3.6, X4.6

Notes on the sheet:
This documentation describes Open Hardware and is licensed under the CERN OHL v. 1.2. You may redistribute and modify this documentation under the terms of the CERN OHL v.1.2. (http://ohwr.org/cernohl). This documentation is distributed WITHOUT ANY EXPRESS OR IMPLIED WARRANTY, INCLUDING OF MERCHANT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
Copyright Oliver Krebs 2016

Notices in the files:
eagle/DFF_1_0.brd:
Licensed under CERN OHL v.1.2
parts and their libraries:
SparkFun-Connectors: Licensing: Creative Commons ShareAlike 4.0 International - https://creativecommons.org/licenses/by-sa/4.0
